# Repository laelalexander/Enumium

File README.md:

# Enumium
Official repository for the Enumium protocol, parent chain architecture, Pulse Network, and SiloBlockchain implementation lineage.

## Robot arm design package
Blueprints, part drawings, wiring schematic and CAD for the desktop robot arm: [`docs/design/README.md`](docs/design/README.md). Generator code: [`3d-workflow/`](3d-workflow/README.md).

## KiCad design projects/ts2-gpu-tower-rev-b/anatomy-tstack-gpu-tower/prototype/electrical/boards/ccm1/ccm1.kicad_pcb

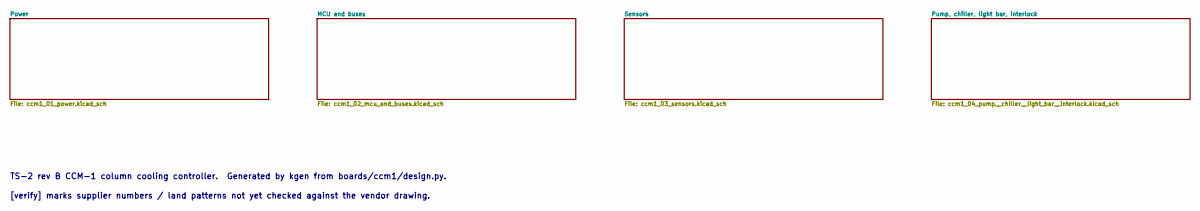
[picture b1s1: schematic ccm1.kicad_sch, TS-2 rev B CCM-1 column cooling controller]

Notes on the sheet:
TS-2 rev B CCM-1 column cooling controller. Generated by kgen from boards/ccm1/design.py.
[verify] marks supplier numbers / land patterns not yet checked against the vendor drawing.

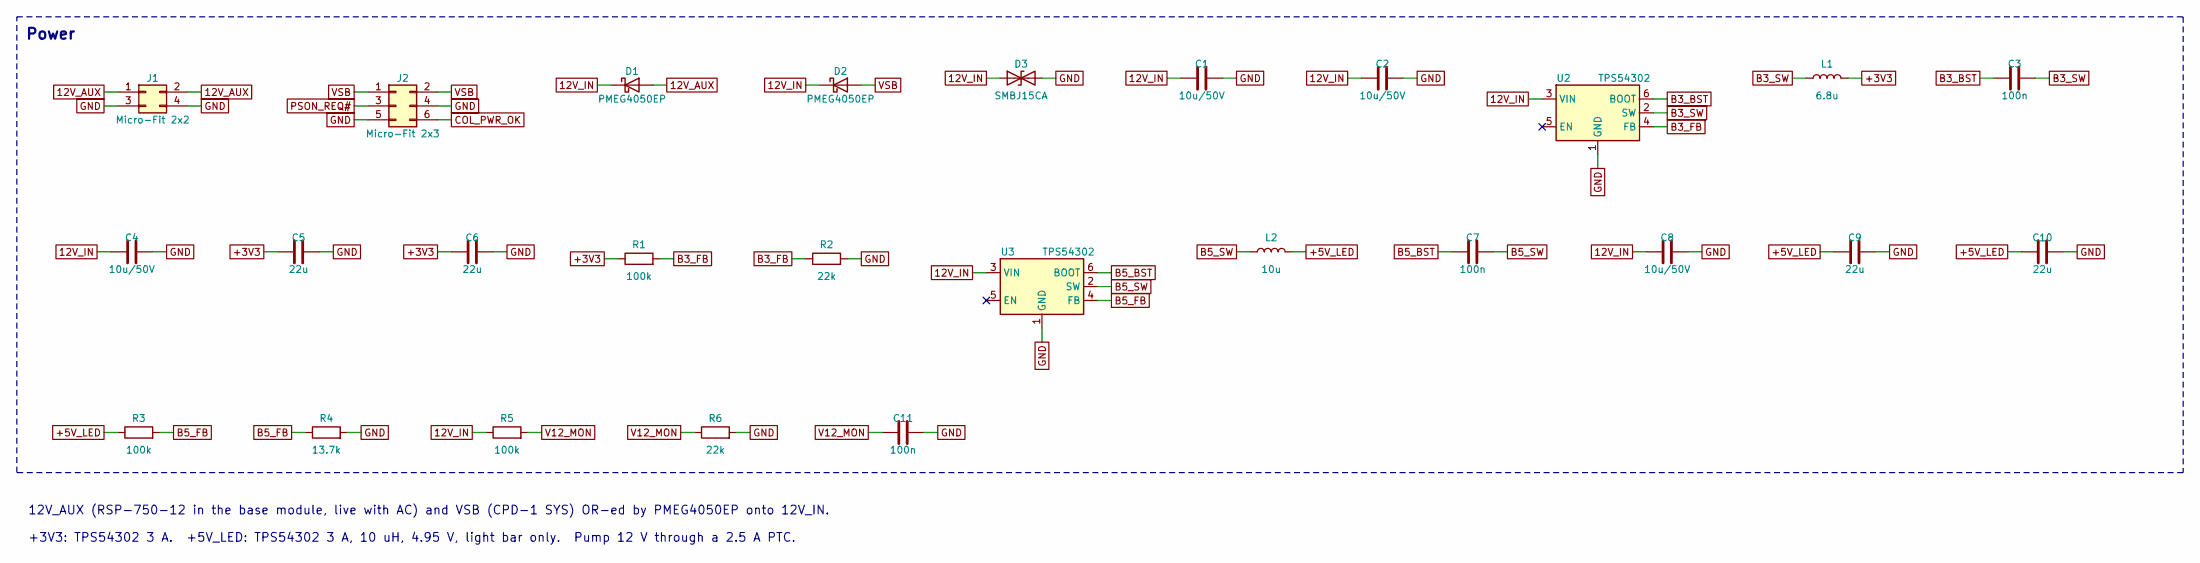
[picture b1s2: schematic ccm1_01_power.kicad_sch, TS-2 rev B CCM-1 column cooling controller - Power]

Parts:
C1, C2, C4, C8: 10u/50V; C_1206_3216Metric; MPN GRM31CR61H106KA12L; LCSC C13585
C3, C7, C11: 100n; C_0603_1608Metric; MPN CL10B104KB8NNNC; LCSC C1591
C5, C6, C9, C10: 22u; C_0805_2012Metric; MPN CL21A226MAQNNNE; LCSC C45783
D1, D2: PMEG4050EP; D_SOD-128; MPN PMEG4050EP,115
D3: SMBJ15CA; D_SMB; MPN SMBJ15CA
J1: Micro-Fit 2x2; Molex_Micro-Fit_3.0_43045-0412_2x02_P3.00mm_Vertical; MPN 43045-0412
J2: Micro-Fit 2x3; Molex_Micro-Fit_3.0_43045-0612_2x03_P3.00mm_Vertical; MPN 43045-0612
L1: 6.8u; L_Bourns_SRP7028A_7.3x6.6mm; MPN SRP7028A-6R8M
L2: 10u; L_Bourns_SRP7028A_7.3x6.6mm; MPN SRP7028A-100M
R1, R3, R5: 100k; R_0603_1608Metric; MPN 0603WAF1003T5E; LCSC C25803
R2, R6: 22k; R_0603_1608Metric; MPN 0603WAF2202T5E; LCSC C31850
R4: 13.7k; R_0603_1608Metric; MPN 0603WAF1372T5E; LCSC C22959
U2, U3: TPS54302; SOT-23-6; MPN TPS54302DDCR

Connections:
12V_AUX: D1.2 (A), J1.1, J1.2
12V_IN: C1.1, C2.1, C4.1, C8.1, D1.1 (K), D2.1 (K), D3.1 (A1), R5.1, U2.3 (VIN), U3.3 (VIN); also elsewhere on the board
+3V3: C5.1, C6.1, L1.2, R1.1; also elsewhere on the board
+5V_LED: C9.1, C10.1, L2.2, R3.1; also elsewhere on the board
B3_BST: C3.1, U2.6 (BOOT)
B3_FB: R1.2, R2.1, U2.4 (FB)
B3_SW: C3.2, L1.1, U2.2 (SW)
B5_BST: C7.1, U3.6 (BOOT)
B5_FB: R3.2, R4.1, U3.4 (FB)
B5_SW: C7.2, L2.1, U3.2 (SW)
COL_PWR_OK: J2.6; also elsewhere on the board
GND: C1.2, C2.2, C4.2, C5.2, C6.2, C8.2, C9.2, C10.2, C11.2, D3.2 (A2), J1.3, J1.4, J2.4, J2.5, R2.2, R4.2, R6.2, U2.1 (GND), U3.1 (GND); also elsewhere on the board
PSON_REQ#: J2.3; also elsewhere on the board
V12_MON: C11.1, R5.2, R6.1; also elsewhere on the board
VSB: D2.2 (A), J2.1, J2.2

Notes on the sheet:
Power
12V_AUX (RSP-750-12 in the base module, live with AC) and VSB (CPD-1 SYS) OR-ed by PMEG4050EP onto 12V_IN.
+3V3: TPS54302 3 A. +5V_LED: TPS54302 3 A, 10 uH, 4.95 V, light bar only. Pump 12 V through a 2.5 A PTC.

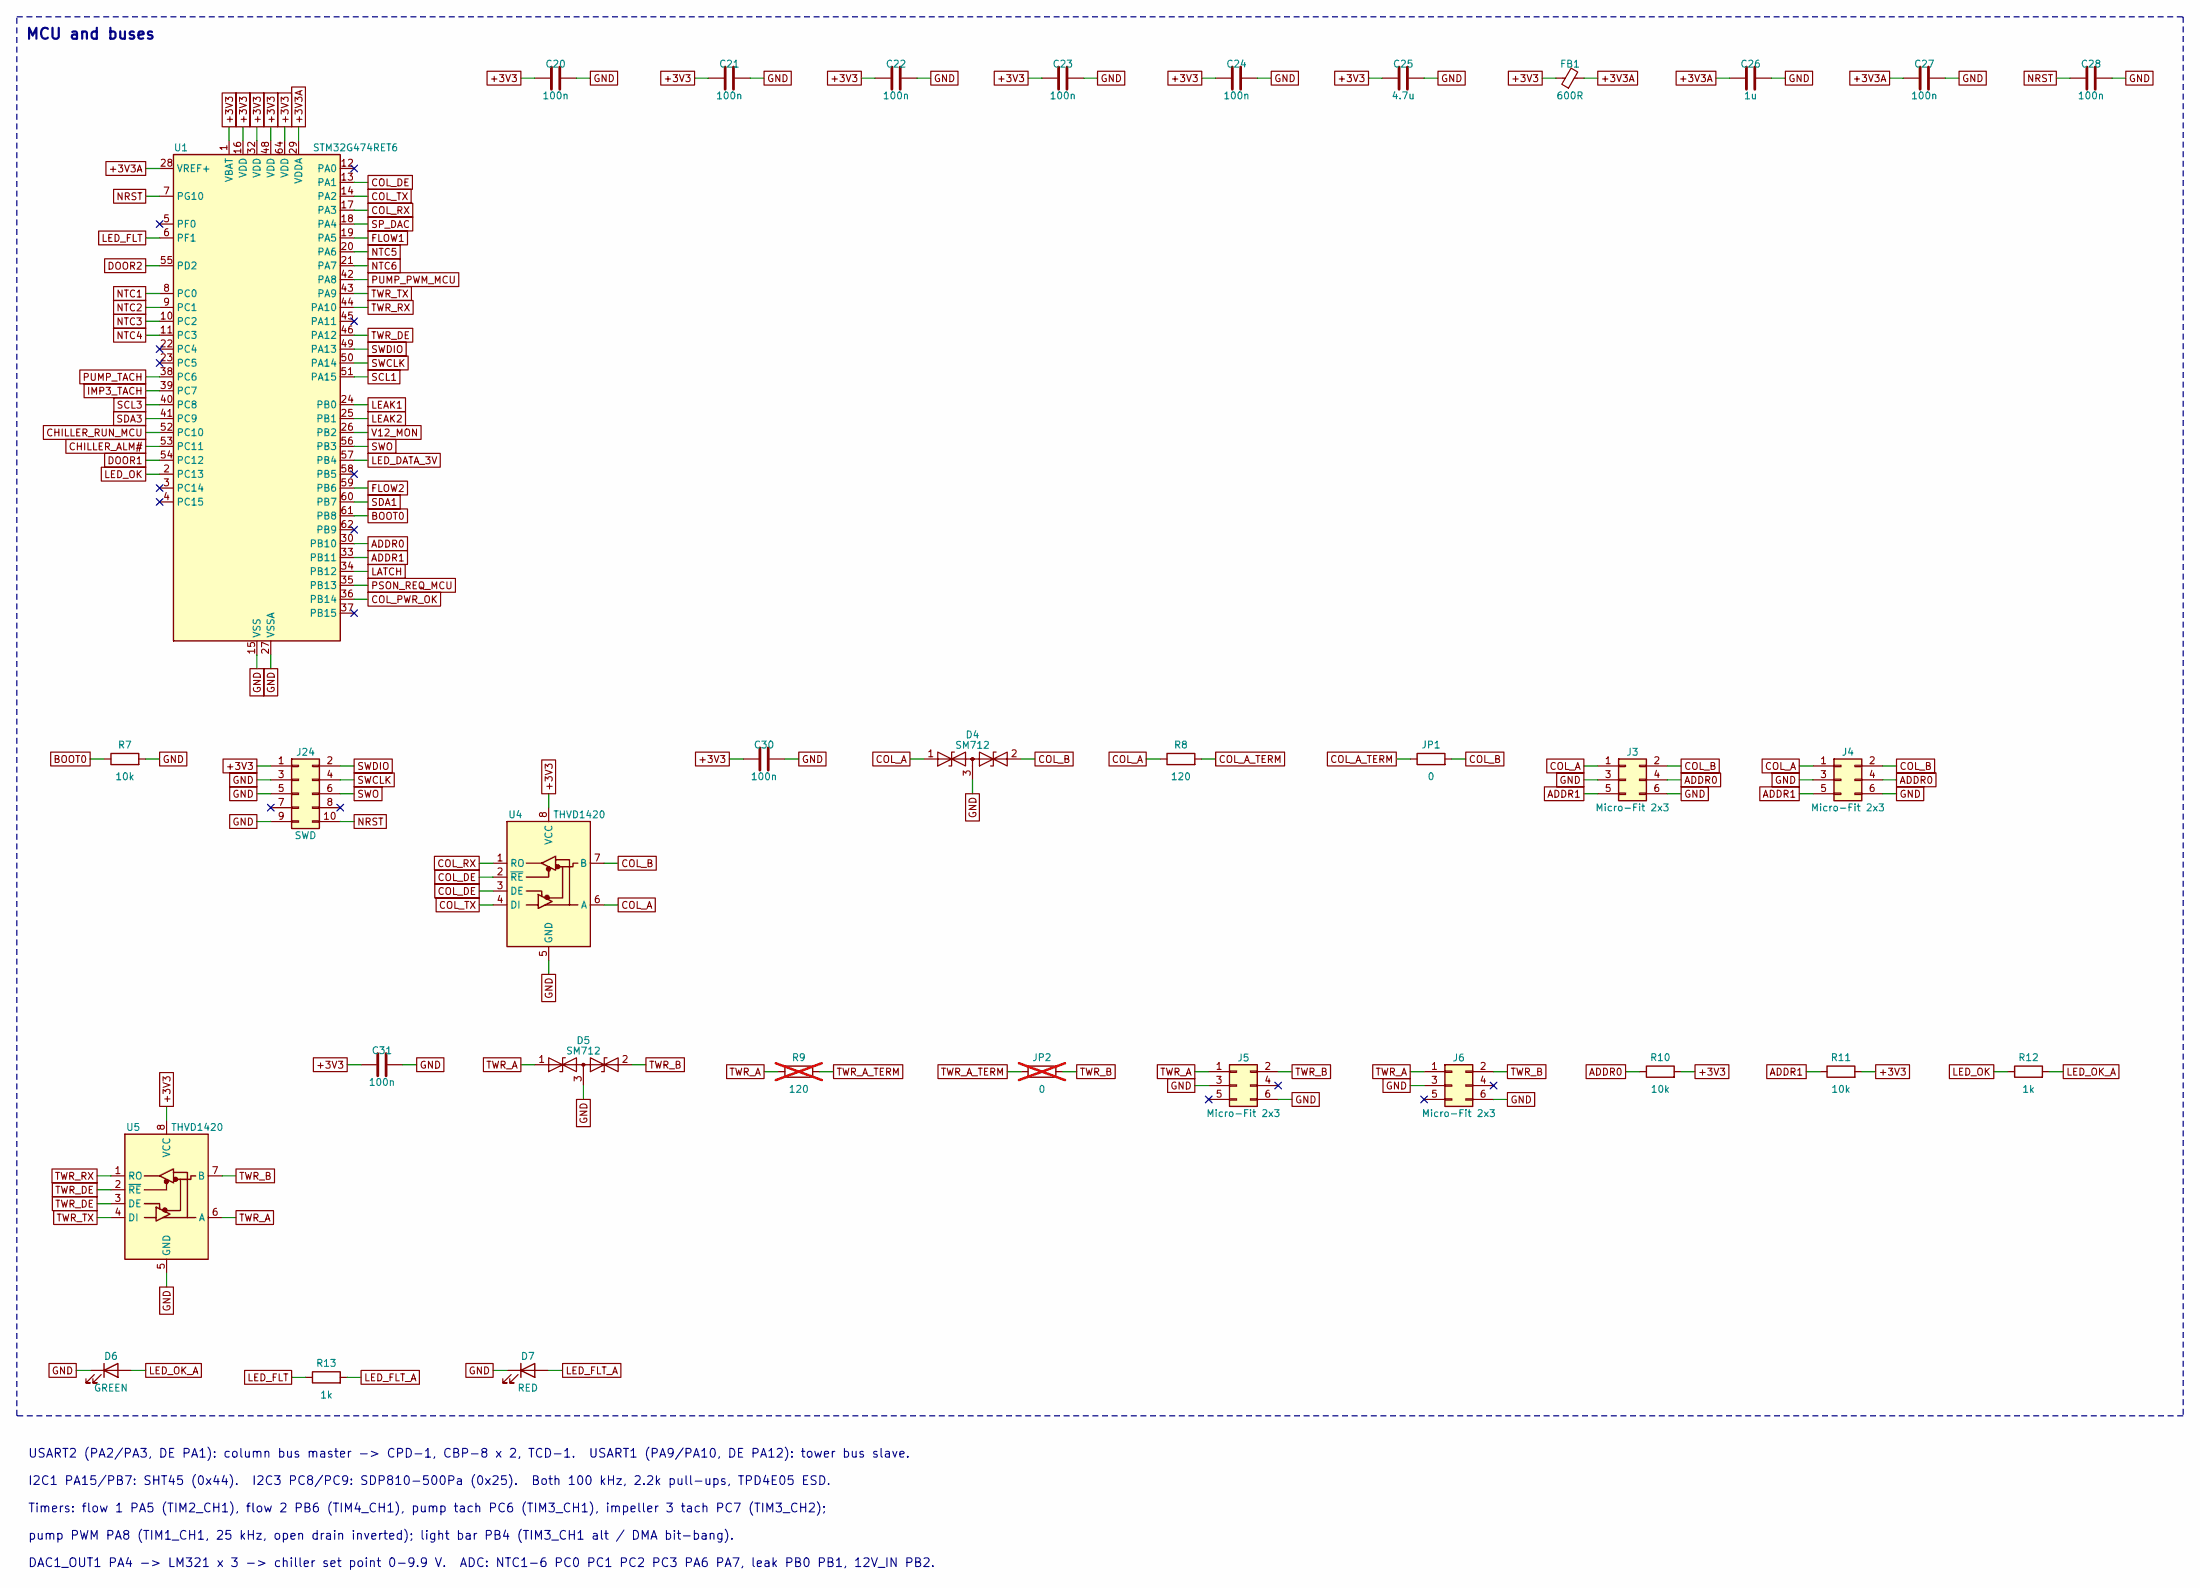
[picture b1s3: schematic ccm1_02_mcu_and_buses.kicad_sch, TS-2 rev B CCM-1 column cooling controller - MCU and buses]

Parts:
C20, C21, C22, C23, C24, C27, C28, C30, C31: 100n; C_0603_1608Metric; MPN CL10B104KB8NNNC; LCSC C1591
C25: 4.7u; C_0603_1608Metric; MPN CL10A475KO8NNNC; LCSC C19666
C26: 1u; C_0603_1608Metric; MPN CL10A105KA8NNNC; LCSC C15849
D4, D5: SM712; SOT-23; MPN SM712.TCT
D6: GREEN; LED_0603_1608Metric; MPN 150060VS75000
D7: RED; LED_0603_1608Metric; MPN 150060RS75000
FB1: 600R; L_0603_1608Metric; MPN BLM18KG601SN1D
J3, J4, J5, J6: Micro-Fit 2x3; Molex_Micro-Fit_3.0_43045-0612_2x03_P3.00mm_Vertical; MPN 43045-0612
J24: SWD; PinHeader_2x05_P1.27mm_Vertical; MPN FTSH-105-01-F-DV-K
JP1: 0; R_0603_1608Metric; MPN 0603WAF0000T5E
JP2: 0; R_0603_1608Metric; MPN 0603WAF0000T5E; not fitted
R7, R10, R11: 10k; R_0603_1608Metric; MPN 0603WAF1002T5E; LCSC C25804
R8: 120; R_0603_1608Metric; MPN 0603WAF1200T5E; LCSC C22787
R9: 120; R_0603_1608Metric; MPN 0603WAF1200T5E; LCSC C22787; not fitted
R12, R13: 1k; R_0603_1608Metric; MPN 0603WAF1001T5E; LCSC C21190
U1: STM32G474RET6; LQFP-64_10x10mm_P0.5mm; MPN STM32G474RET6
U4, U5: THVD1420; SOIC-8_3.9x4.9mm_P1.27mm; MPN THVD1420DR

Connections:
+3V3: C20.1, C21.1, C22.1, C23.1, C24.1, C25.1, C30.1, C31.1, FB1.1, J24.1, R10.2, R11.2, U1.1 (VBAT), U1.16 (VDD), U1.32 (VDD), U1.48 (VDD), U1.64 (VDD), U4.8 (VCC), U5.8 (VCC); also elsewhere on the board
+3V3A: C26.1, C27.1, FB1.2, U1.28 (VREF+), U1.29 (VDDA); also elsewhere on the board
ADDR0: J3.4, J4.4, R10.1, U1.30 (PB10)
ADDR1: J3.5, J4.5, R11.1, U1.33 (PB11)
BOOT0: R7.1, U1.61 (PB8)
CHILLER_ALM#: U1.53 (PC11); also elsewhere on the board
CHILLER_RUN_MCU: U1.52 (PC10); also elsewhere on the board
COL_A: D4.1 (A1), J3.1, J4.1, R8.1, U4.6 (A)
COL_A_TERM: JP1.1, R8.2
COL_B: D4.2 (A2), J3.2, J4.2, JP1.2, U4.7 (B)
COL_DE: U1.13 (PA1), U4.2 (~RE), U4.3 (DE)
COL_PWR_OK: U1.36 (PB14); also elsewhere on the board
COL_RX: U1.17 (PA3), U4.1 (RO)
COL_TX: U1.14 (PA2), U4.4 (DI)
DOOR1: U1.54 (PC12); also elsewhere on the board
DOOR2: U1.55 (PD2); also elsewhere on the board
FLOW1: U1.19 (PA5); also elsewhere on the board
FLOW2: U1.59 (PB6); also elsewhere on the board
GND: C20.2, C21.2, C22.2, C23.2, C24.2, C25.2, C26.2, C27.2, C28.2, C30.2, C31.2, D4.3 (common), D5.3 (common), D6.1 (K), D7.1 (K), J3.3, J3.6, J4.3, J4.6, J5.3, J5.6, J6.3, J6.6, J24.3, J24.5, J24.9, R7.2, U1.15 (VSS), U1.27 (VSSA), U1.31 (VSS), U1.47 (VSS), U1.63 (VSS), U4.5 (GND), U5.5 (GND); also elsewhere on the board
IMP3_TACH: U1.39 (PC7); also elsewhere on the board
LATCH: U1.34 (PB12); also elsewhere on the board
LEAK1: U1.24 (PB0); also elsewhere on the board
LEAK2: U1.25 (PB1); also elsewhere on the board
LED_DATA_3V: U1.57 (PB4); also elsewhere on the board
LED_FLT: R13.1, U1.6 (PF1)
LED_FLT_A: D7.2 (A), R13.2
LED_OK: R12.1, U1.2 (PC13)
LED_OK_A: D6.2 (A), R12.2
NRST: C28.1, J24.10, U1.7 (PG10)
NTC1: U1.8 (PC0); also elsewhere on the board
NTC2: U1.9 (PC1); also elsewhere on the board
NTC3: U1.10 (PC2); also elsewhere on the board
NTC4: U1.11 (PC3); also elsewhere on the board
NTC5: U1.20 (PA6); also elsewhere on the board
NTC6: U1.21 (PA7); also elsewhere on the board
PSON_REQ_MCU: U1.35 (PB13); also elsewhere on the board
PUMP_PWM_MCU: U1.42 (PA8); also elsewhere on the board
PUMP_TACH: U1.38 (PC6); also elsewhere on the board
SCL1: U1.51 (PA15); also elsewhere on the board
SCL3: U1.40 (PC8); also elsewhere on the board
SDA1: U1.60 (PB7); also elsewhere on the board
SDA3: U1.41 (PC9); also elsewhere on the board
SP_DAC: U1.18 (PA4); also elsewhere on the board
SWCLK: J24.4, U1.50 (PA14)
SWDIO: J24.2, U1.49 (PA13)
SWO: J24.6, U1.56 (PB3)
TWR_A: D5.1 (A1), J5.1, J6.1, R9.1, U5.6 (A)
TWR_A_TERM: JP2.1, R9.2
TWR_B: D5.2 (A2), J5.2, J6.2, JP2.2, U5.7 (B)
TWR_DE: U1.46 (PA12), U5.2 (~RE), U5.3 (DE)
TWR_RX: U1.44 (PA10), U5.1 (RO)
TWR_TX: U1.43 (PA9), U5.4 (DI)
V12_MON: U1.26 (PB2); also elsewhere on the board

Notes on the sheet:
MCU and buses
USART2 (PA2/PA3, DE PA1): column bus master -> CPD-1, CBP-8 x 2, TCD-1. USART1 (PA9/PA10, DE PA12): tower bus slave.
I2C1 PA15/PB7: SHT45 (0x44). I2C3 PC8/PC9: SDP810-500Pa (0x25). Both 100 kHz, 2.2k pull-ups, TPD4E05 ESD.
Timers: flow 1 PA5 (TIM2_CH1), flow 2 PB6 (TIM4_CH1), pump tach PC6 (TIM3_CH1), impeller 3 tach PC7 (TIM3_CH2);
pump PWM PA8 (TIM1_CH1, 25 kHz, open drain inverted); light bar PB4 (TIM3_CH1 alt / DMA bit-bang).
DAC1_OUT1 PA4 -> LM321 x 3 -> chiller set point 0-9.9 V. ADC: NTC1-6 PC0 PC1 PC2 PC3 PA6 PA7, leak PB0 PB1, 12V_IN PB2.

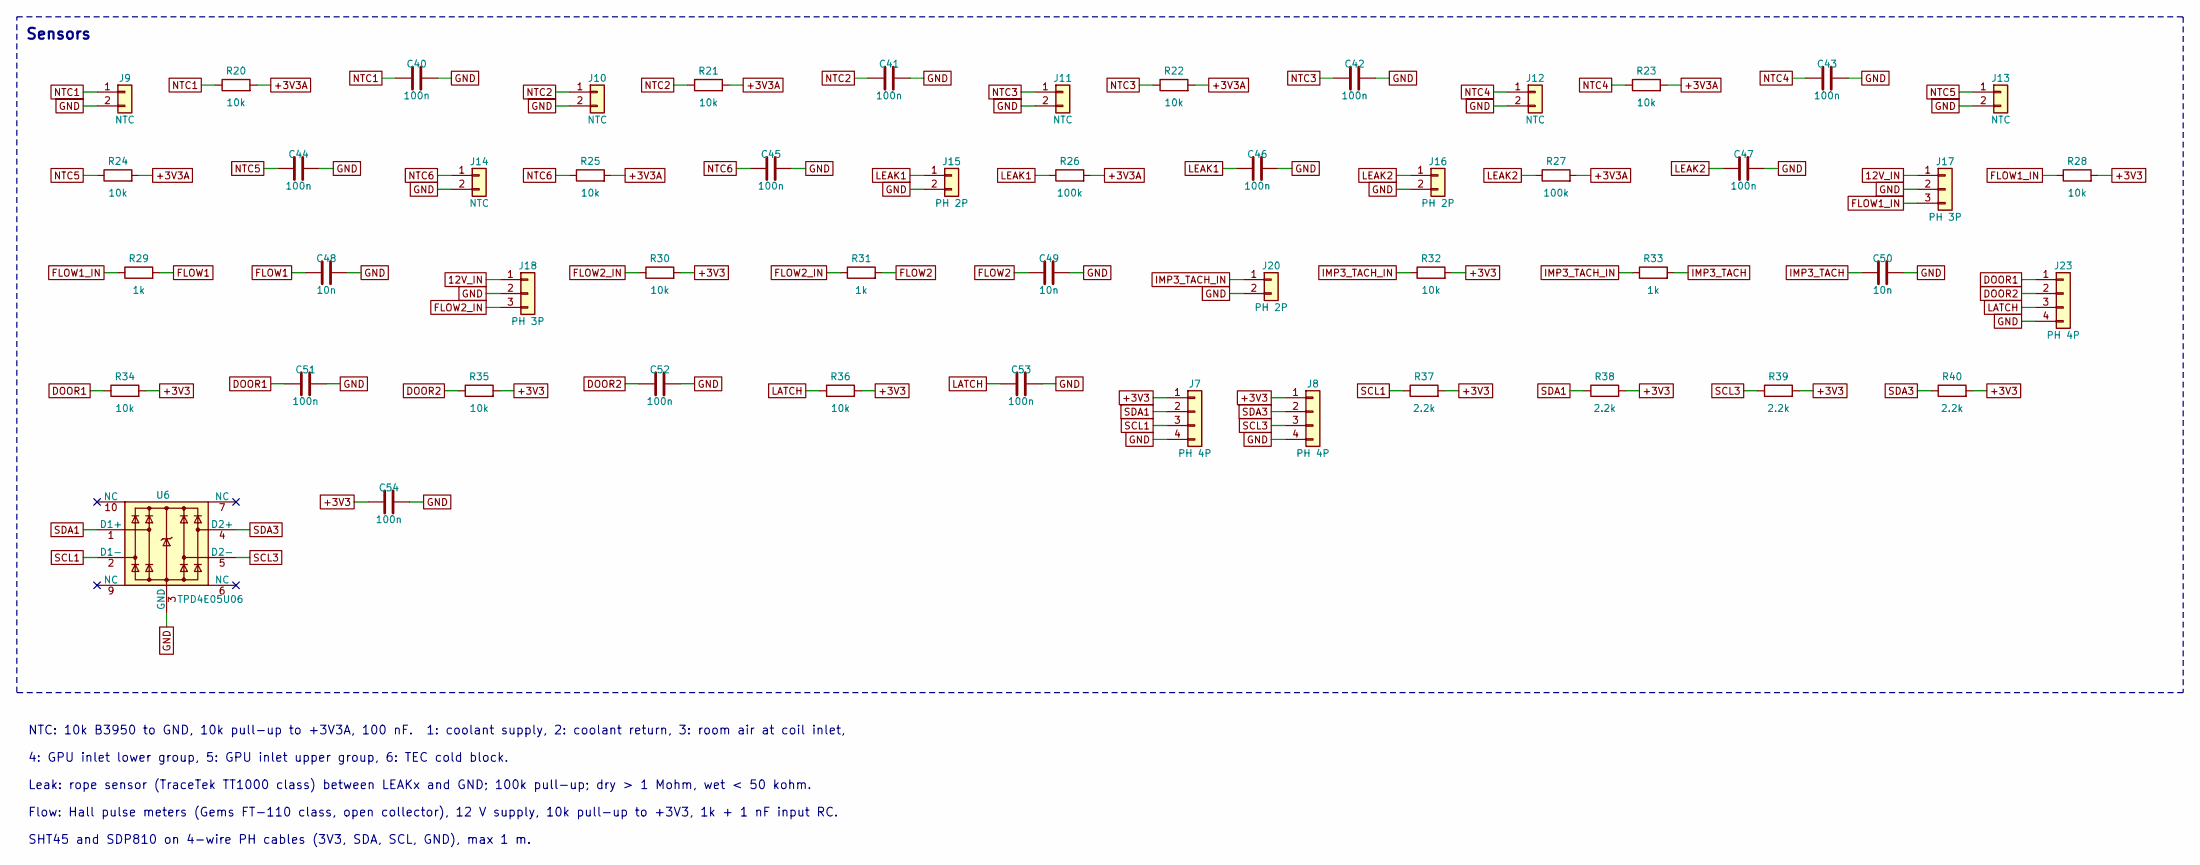
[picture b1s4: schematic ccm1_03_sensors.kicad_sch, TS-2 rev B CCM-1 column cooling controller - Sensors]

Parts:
C40, C41, C42, C43, C44, C45, C46, C47, C51, C52, C53, C54: 100n; C_0603_1608Metric; MPN CL10B104KB8NNNC; LCSC C1591
C48, C49, C50: 10n; C_0603_1608Metric; MPN CL10B103KB8NNNC; LCSC C57112
J7, J8, J23: PH 4P; JST_PH_B4B-PH-K_1x04_P2.00mm_Vertical; MPN B4B-PH-K-S
J9, J10, J11, J12, J13, J14: NTC; JST_PH_B2B-PH-K_1x02_P2.00mm_Vertical; MPN B2B-PH-K-S
J15, J16, J20: PH 2P; JST_PH_B2B-PH-K_1x02_P2.00mm_Vertical; MPN B2B-PH-K-S
J17, J18: PH 3P; JST_PH_B3B-PH-K_1x03_P2.00mm_Vertical; MPN B3B-PH-K-S
R20, R21, R22, R23, R24, R25, R28, R30, R32, R34, R35, R36: 10k; R_0603_1608Metric; MPN 0603WAF1002T5E; LCSC C25804
R26, R27: 100k; R_0603_1608Metric; MPN 0603WAF1003T5E; LCSC C25803
R29, R31, R33: 1k; R_0603_1608Metric; MPN 0603WAF1001T5E; LCSC C21190
R37, R38, R39, R40: 2.2k; R_0603_1608Metric; MPN 0603WAF2201T5E; LCSC C4190
U6: TPD4E05U06; USON-10_2.5x1.0mm_P0.5mm; MPN TPD4E05U06DQAR

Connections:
12V_IN: J17.1, J18.1; also elsewhere on the board
+3V3: C54.1, J7.1, J8.1, R28.2, R30.2, R32.2, R34.2, R35.2, R36.2, R37.2, R38.2, R39.2, R40.2; also elsewhere on the board
+3V3A: R20.2, R21.2, R22.2, R23.2, R24.2, R25.2, R26.2, R27.2; also elsewhere on the board
DOOR1: C51.1, J23.1, R34.1; also elsewhere on the board
DOOR2: C52.1, J23.2, R35.1; also elsewhere on the board
FLOW1: C48.1, R29.2; also elsewhere on the board
FLOW1_IN: J17.3, R28.1, R29.1
FLOW2: C49.1, R31.2; also elsewhere on the board
FLOW2_IN: J18.3, R30.1, R31.1
GND: C40.2, C41.2, C42.2, C43.2, C44.2, C45.2, C46.2, C47.2, C48.2, C49.2, C50.2, C51.2, C52.2, C53.2, C54.2, J7.4, J8.4, J9.2, J10.2, J11.2, J12.2, J13.2, J14.2, J15.2, J16.2, J17.2, J18.2, J20.2, J23.4, U6.3 (GND), U6.8 (GND); also elsewhere on the board
IMP3_TACH: C50.1, R33.2; also elsewhere on the board
IMP3_TACH_IN: J20.1, R32.1, R33.1
LATCH: C53.1, J23.3, R36.1; also elsewhere on the board
LEAK1: C46.1, J15.1, R26.1; also elsewhere on the board
LEAK2: C47.1, J16.1, R27.1; also elsewhere on the board
NTC1: C40.1, J9.1, R20.1; also elsewhere on the board
NTC2: C41.1, J10.1, R21.1; also elsewhere on the board
NTC3: C42.1, J11.1, R22.1; also elsewhere on the board
NTC4: C43.1, J12.1, R23.1; also elsewhere on the board
NTC5: C44.1, J13.1, R24.1; also elsewhere on the board
NTC6: C45.1, J14.1, R25.1; also elsewhere on the board
SCL1: J7.3, R37.1, U6.2 (D1-); also elsewhere on the board
SCL3: J8.3, R39.1, U6.5 (D2-); also elsewhere on the board
SDA1: J7.2, R38.1, U6.1 (D1+); also elsewhere on the board
SDA3: J8.2, R40.1, U6.4 (D2+); also elsewhere on the board

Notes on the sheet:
Sensors
NTC: 10k B3950 to GND, 10k pull-up to +3V3A, 100 nF. 1: coolant supply, 2: coolant return, 3: room air at coil inlet,
4: GPU inlet lower group, 5: GPU inlet upper group, 6: TEC cold block.
Leak: rope sensor (TraceTek TT1000 class) between LEAKx and GND; 100k pull-up; dry > 1 Mohm, wet < 50 kohm.
Flow: Hall pulse meters (Gems FT-110 class, open collector), 12 V supply, 10k pull-up to +3V3, 1k + 1 nF input RC.
SHT45 and SDP810 on 4-wire PH cables (3V3, SDA, SCL, GND), max 1 m.

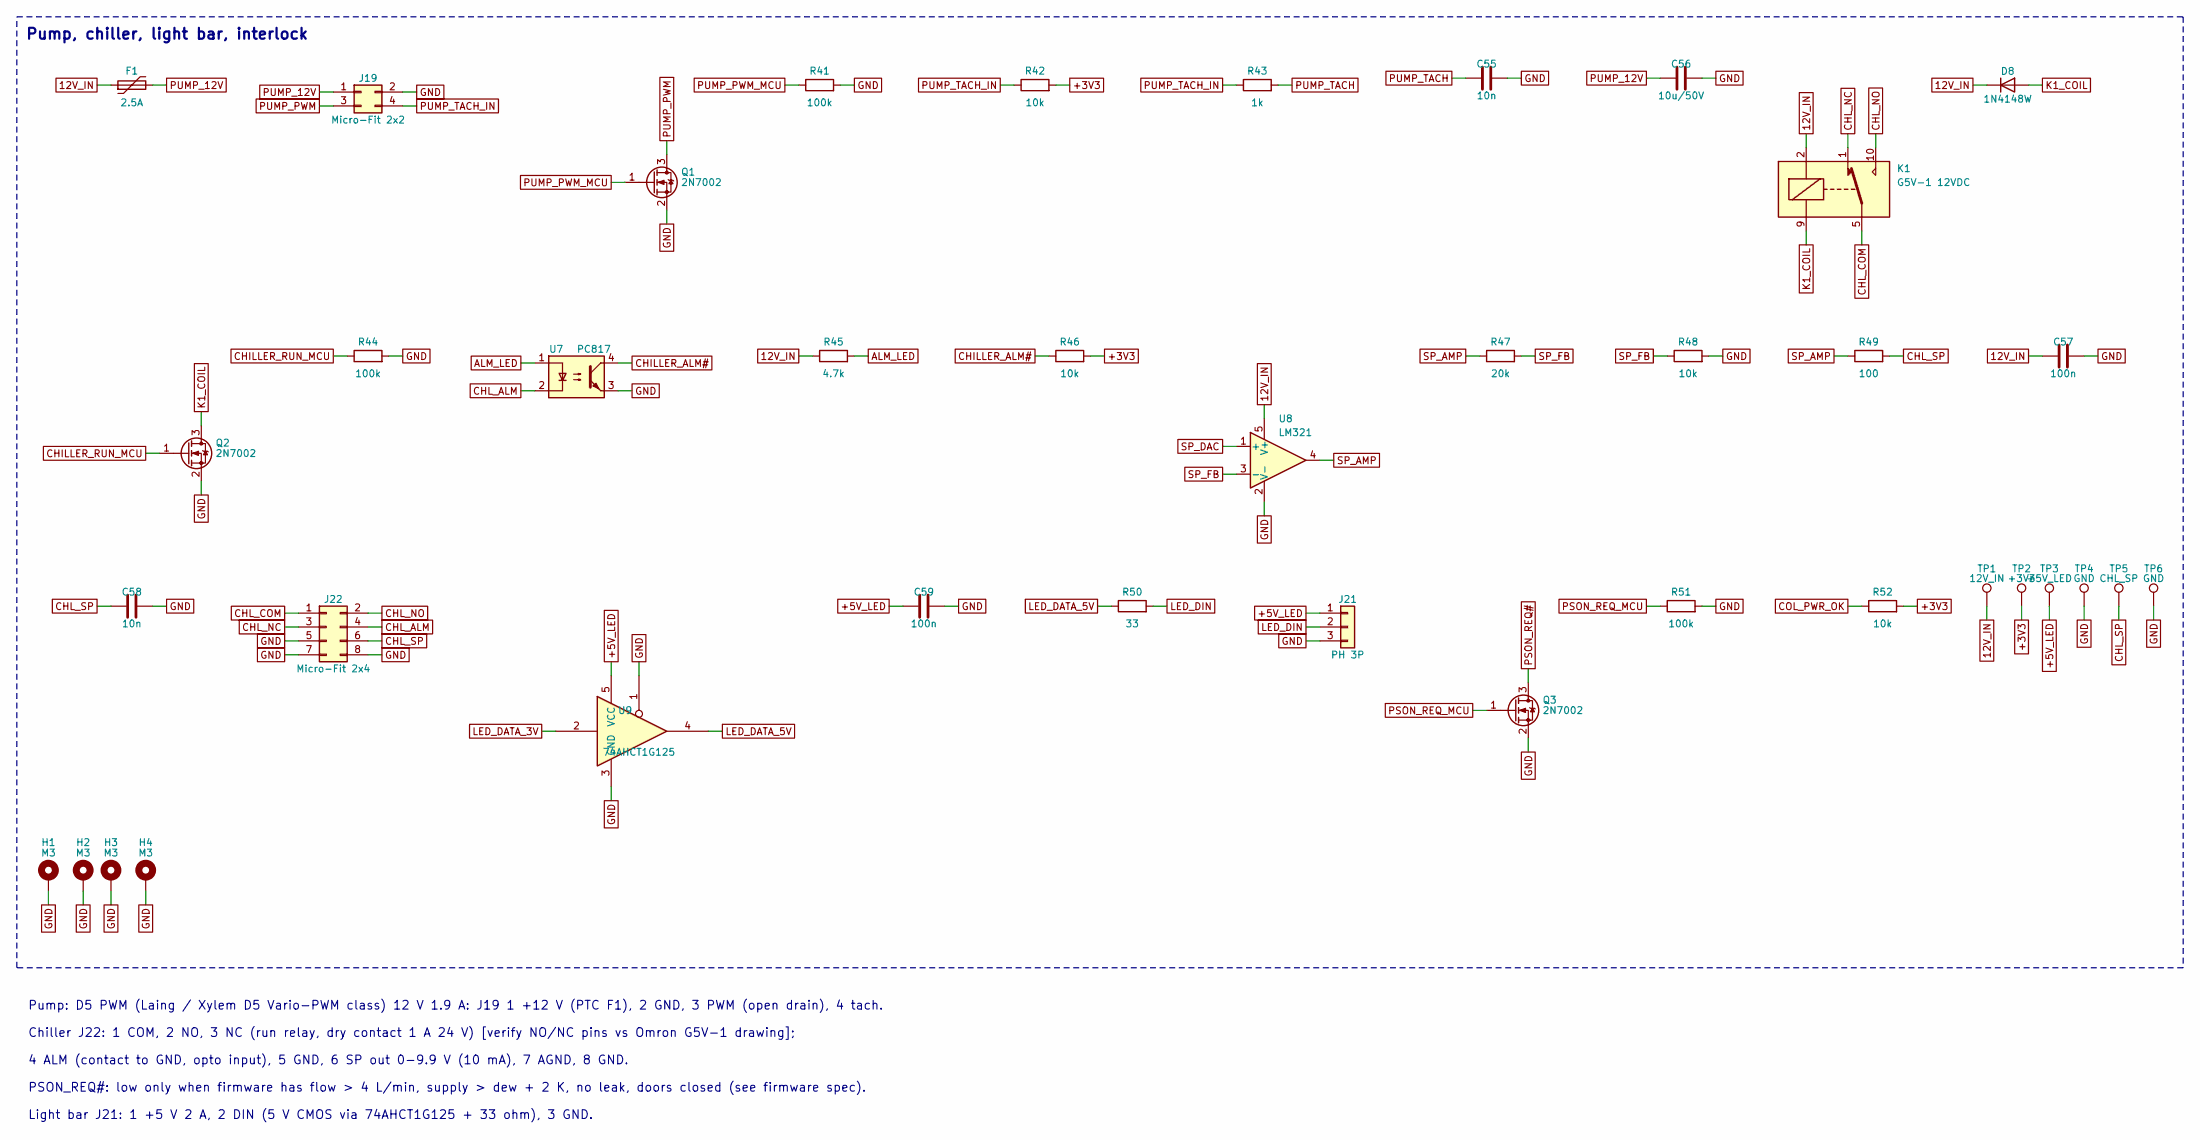
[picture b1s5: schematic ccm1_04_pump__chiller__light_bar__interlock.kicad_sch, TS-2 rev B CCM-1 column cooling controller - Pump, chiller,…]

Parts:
C55, C58: 10n; C_0603_1608Metric; MPN CL10B103KB8NNNC; LCSC C57112
C56: 10u/50V; C_1206_3216Metric; MPN GRM31CR61H106KA12L; LCSC C13585
C57, C59: 100n; C_0603_1608Metric; MPN CL10B104KB8NNNC; LCSC C1591
D8: 1N4148W; D_SOD-123; MPN 1N4148W-7-F
F1: 2.5A; Fuse_1812_4532Metric; MPN MF-MSMF250/16X-2
H1, H2, H3, H4: M3; MountingHole_3.2mm_M3_Pad_Via
J19: Micro-Fit 2x2; Molex_Micro-Fit_3.0_43045-0412_2x02_P3.00mm_Vertical; MPN 43045-0412
J21: PH 3P; JST_PH_B3B-PH-K_1x03_P2.00mm_Vertical; MPN B3B-PH-K-S
J22: Micro-Fit 2x4; Molex_Micro-Fit_3.0_43045-0812_2x04_P3.00mm_Vertical; MPN 43045-0812
K1: G5V-1 12VDC; Relay_SPDT_Omron_G5V-1; MPN G5V-1-DC12
Q1, Q2, Q3: 2N7002; SOT-23; MPN 2N7002,215
R41, R44, R51: 100k; R_0603_1608Metric; MPN 0603WAF1003T5E; LCSC C25803
R42, R46, R48, R52: 10k; R_0603_1608Metric; MPN 0603WAF1002T5E; LCSC C25804
R43: 1k; R_0603_1608Metric; MPN 0603WAF1001T5E; LCSC C21190
R45: 4.7k; R_0603_1608Metric; MPN 0603WAF4701T5E; LCSC C23162
R47: 20k; R_0603_1608Metric; MPN 0603WAF2002T5E; LCSC C4184
R49: 100; R_0603_1608Metric; MPN 0603WAF1000T5E; LCSC C22775
R50: 33; R_0603_1608Metric; MPN 0603WAF330JT5E; LCSC C23140
TP1: 12V_IN; TestPoint_Pad_D1.5mm
TP2: +3V3; TestPoint_Pad_D1.5mm
TP3: +5V_LED; TestPoint_Pad_D1.5mm
TP4, TP6: GND; TestPoint_Pad_D1.5mm
TP5: CHL_SP; TestPoint_Pad_D1.5mm
U7: PC817; SMDIP-4_W9.53mm; MPN PC817X2NSZ9F
U8: LM321; SOT-23-5; MPN LM321MF/NOPB
U9: 74AHCT1G125; SOT-23-5; MPN SN74AHCT1G125DBVR

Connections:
12V_IN: C57.1, D8.1 (K), F1.1, K1.2, R45.1, TP1.1, U8.5 (V+); also elsewhere on the board
+3V3: R42.2, R46.2, R52.2, TP2.1; also elsewhere on the board
+5V_LED: C59.1, J21.1, TP3.1, U9.5 (VCC); also elsewhere on the board
ALM_LED: R45.2, U7.1
CHILLER_ALM#: R46.1, U7.4; also elsewhere on the board
CHILLER_RUN_MCU: Q2.1 (G), R44.1; also elsewhere on the board
CHL_ALM: J22.4, U7.2
CHL_COM: J22.1, K1.5, K1.6
CHL_NC: J22.3, K1.1
CHL_NO: J22.2, K1.10
CHL_SP: C58.1, J22.6, R49.2, TP5.1
COL_PWR_OK: R52.1; also elsewhere on the board
GND: C55.2, C56.2, C57.2, C58.2, C59.2, H1.1, H2.1, H3.1, H4.1, J19.2, J21.3, J22.5, J22.7, J22.8, Q1.2 (S), Q2.2 (S), Q3.2 (S), R41.2, R44.2, R48.2, R51.2, TP4.1, TP6.1, U7.3, U8.2 (V-), U9.1, U9.3 (GND); also elsewhere on the board
K1_COIL: D8.2 (A), K1.9, Q2.3 (D)
LED_DATA_3V: U9.2; also elsewhere on the board
LED_DATA_5V: R50.1, U9.4
LED_DIN: J21.2, R50.2
PSON_REQ#: Q3.3 (D); also elsewhere on the board
PSON_REQ_MCU: Q3.1 (G), R51.1; also elsewhere on the board
PUMP_12V: C56.1, F1.2, J19.1
PUMP_PWM: J19.3, Q1.3 (D)
PUMP_PWM_MCU: Q1.1 (G), R41.1; also elsewhere on the board
PUMP_TACH: C55.1, R43.2; also elsewhere on the board
PUMP_TACH_IN: J19.4, R42.1, R43.1
SP_AMP: R47.1, R49.1, U8.4
SP_DAC: U8.1 (+); also elsewhere on the board
SP_FB: R47.2, R48.1, U8.3 (-)

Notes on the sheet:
Pump, chiller, light bar, interlock
Pump: D5 PWM (Laing / Xylem D5 Vario-PWM class) 12 V 1.9 A: J19 1 +12 V (PTC F1), 2 GND, 3 PWM (open drain), 4 tach.
Chiller J22: 1 COM, 2 NO, 3 NC (run relay, dry contact 1 A 24 V) [verify NO/NC pins vs Omron G5V-1 drawing];
4 ALM (contact to GND, opto input), 5 GND, 6 SP out 0-9.9 V (10 mA), 7 AGND, 8 GND.
PSON_REQ#: low only when firmware has flow > 4 L/min, supply > dew + 2 K, no leak, doors closed (see firmware spec).
Light bar J21: 1 +5 V 2 A, 2 DIN (5 V CMOS via 74AHCT1G125 + 33 ohm), 3 GND.

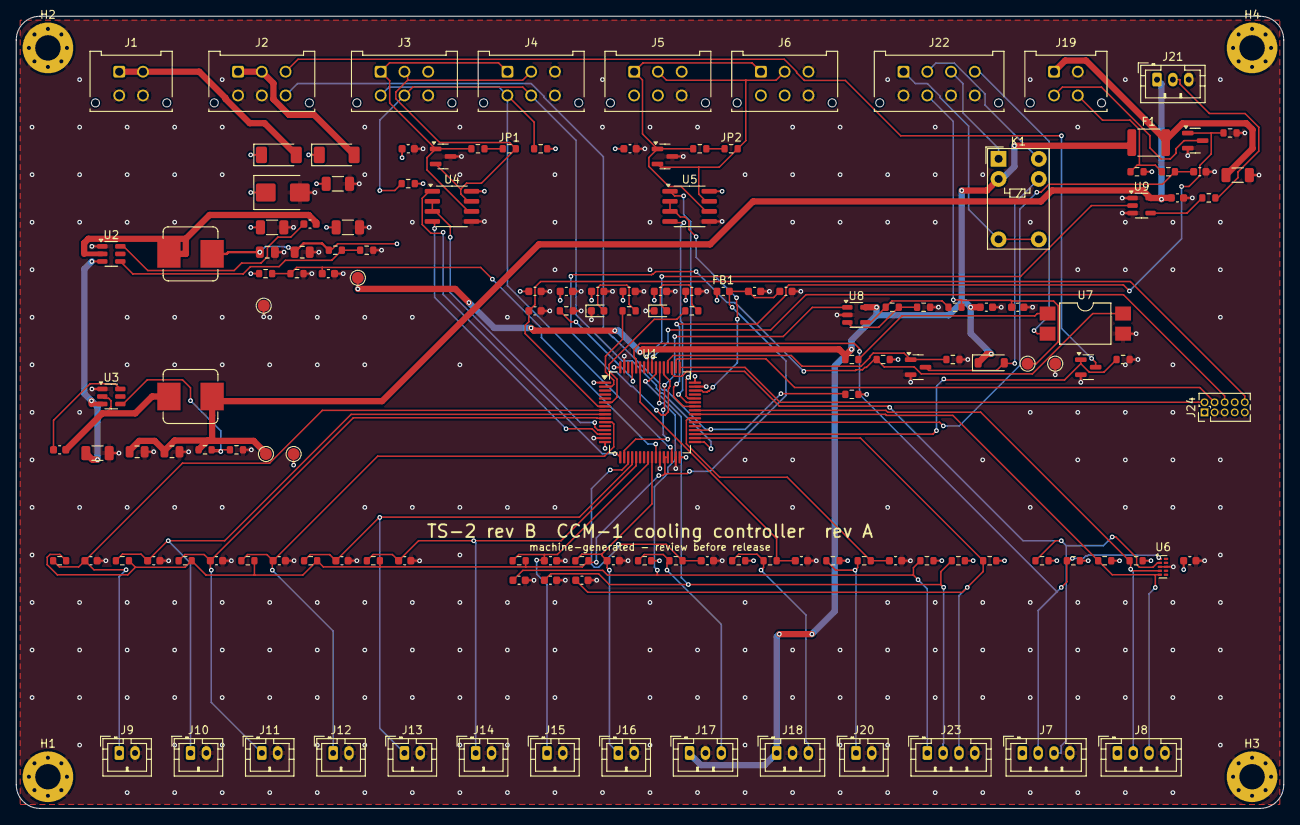
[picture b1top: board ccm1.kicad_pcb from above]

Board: 4 copper layers, 160.0 x 100.0 mm, 149 parts (0 on the bottom side), 81 nets.

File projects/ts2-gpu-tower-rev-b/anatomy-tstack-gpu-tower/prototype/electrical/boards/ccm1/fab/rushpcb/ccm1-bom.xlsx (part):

CCM1 TS-2 rev B CCM-1 column cooling controller rev A - Bill of Materials (qty 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
Item | Qty | Designators | Value | Description | Manufacturer | MPN | Supplier PN | Footprint | Side | DNP | Unit price USD (est.) | Ext. USD (est.)
1 | 5 | C1 C2 C4 C8 C56 | 10u/50V | MLCC 10 uF 50 V X5R 1206 | Murata | GRM31CR61H106KA12L | LCSC C13585 | C_1206_3216Metric | Top |  | 0.06 | 0.3
2 | 4 | C5 C6 C9 C10 | 22u | MLCC 22 uF 25 V X5R 0805 | Samsung Electro-Mechanics | CL21A226MAQNNNE | LCSC C45783 | C_0805_2012Metric | Top |  | 0.06 | 0.24
3 | 26 | C3 C7 C11 C20 C21 C22 C23 C24 C27 C28 C30 C31 C40 C41 C42 C43 C44 C45 C46 C47 C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 | 100n | Bootstrap 100 nF | Samsung Electro-Mechanics | CL10B104KB8NNNC | LCSC C1591 | C_0603_1608Metric | Top |  | 0.01 | 0.26
4 | 1 | C25 | 4.7u | MLCC 4.7 uF 16 V X5R 0603 | Samsung Electro-Mechanics | CL10A475KO8NNNC | LCSC C19666 | C_0603_1608Metric | Top |  | 0.01 | 0.01
5 | 1 | C26 | 1u | VDDA decoupling | Samsung Electro-Mechanics | CL10A105KA8NNNC | LCSC C15849 | C_0603_1608Metric | Top |  | 0.01 | 0.01
6 | 5 | C48 C49 C50 C55 C58 | 10n | input filter (pulses < 2 kHz) | Samsung Electro-Mechanics | CL10B103KB8NNNC | LCSC C57112 | C_0603_1608Metric | Top |  | 0.01 | 0.05
7 | 2 | D1 D2 | PMEG4050EP | Schottky 40 V 5 A SOD-128, supply OR-ing | Nexperia | PMEG4050EP,115 | 1727-4993-1-ND [verify] | D_SOD-128 | Top |  | 0.35 | 0.7
8 | 1 | D3 | SMBJ15CA | TVS 15 V 600 W, 12V_IN | Littelfuse | SMBJ15CA | SMBJ15CALFCT-ND [verify] | D_SMB | Top |  | 0.3 | 0.3
9 | 2 | D4 D5 | SM712 | RS-485 TVS -7 / +12 V asymmetric | Semtech | SM712.TCT | SM712.TCTCT-ND [verify] | SOT-23 | Top |  | 0.4 | 0.8
10 | 1 | D6 | GREEN | LED green 0603 | Wurth Elektronik | 150060VS75000 | [verify] | LED_0603_1608Metric | Top |  | 0.15 | 0.15
11 | 1 | D7 | RED | LED red 0603 | Wurth Elektronik | 150060RS75000 | [verify] | LED_0603_1608Metric | Top |  | 0.15 | 0.15
12 | 1 | D8 | 1N4148W | Relay coil flyback | Diodes Inc | 1N4148W-7-F | 1N4148W-FDICT-ND | D_SOD-123 | Top |  | 0.05 | 0.05
13 | 1 | F1 | 2.5A | PTC 2.5 A hold 16 V 1812, pump supply | Bourns | MF-MSMF250/16X-2 | MF-MSMF250/16X-2CT-ND [verify] | Fuse_1812_4532Metric | Top |  | 0.4 | 0.4
14 | 1 | FB1 | 600R | Ferrite 600 ohm @ 100 MHz, VDDA / VREF+ filter | Murata | BLM18KG601SN1D | 490-5258-1-ND [verify] | L_0603_1608Metric | Top |  | 0.1 | 0.1
15 | 2 | J1 J19 | Micro-Fit 2x2 | 12V_AUX in from RSP-750-12: 1/2 +12 V, 3/4 GND (mating 43025-0400 + 43030 crimp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 | Molex | 43045-0412 | [verify] | Molex_Micro-Fit_3.0_43045-0412_2x02_P3.00mm_Vertical | Top |  | 1.2 | 2.4
16 | 5 | J2 J3 J4 J5 J6 | Micro-Fit 2x3 | CPD-1 SYS: 1/2 VSB in, 3 PSON_REQ# out (open drain), 4/5 GND, 6 COL_PWR_OK in (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 | Molex | 43045-0612 | [verify] | Molex_Micro-Fit_3.0_43045-0612_2x03_P3.00mm_Vertical | Top |  | 1.2 | 6
17 | 6 | J9 J10 J11 J12 J13 J14 | NTC | NTC 10k B3950 cable sensor: coolant supply | JST | B2B-PH-K-S | 455-1704-ND | JST_PH_B2B-PH-K_1x02_P2.00mm_Vertical | Top |  | 0.2 | 1.2
18 | 3 | J15 J16 J20 | PH 2P | Leak rope sensor 1 (coil drip tray) (mating PHR-2 + SPH-002T-P0.5S) | JST | B2B-PH-K-S | [verify] | JST_PH_B2B-PH-K_1x02_P2.00mm_Vertical | Top |  | 0.2 | 0.6
19 | 3 | J17 J18 J21 | PH 3P | Flow meter 1 (column supply): 1 +12 V, 2 GND, 3 pulse (mating PHR-3 + SPH-002T-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 | JST | B3B-PH-K-S | [verify] | JST_PH_B3B-PH-K_1x03_P2.00mm_Vertical | Top |  | 0.2 | 0.6
20 | 1 | J22 | Micro-Fit 2x4 | Chiller: 1 COM, 2 NO, 3 NC, 4 ALM, 5 GND, 6 SP 0-9.9 V, 7 AGND, 8 GND (mating 4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 | Molex | 43045-0812 | [verify] | Molex_Micro-Fit_3.0_43045-0812_2x04_P3.00mm_Vertical | Top |  | 1.2 | 1.2
21 | 3 | J7 J8 J23 | PH 4P | Switches to GND: 1 service door, 2 crown access, 3 coil latch (mating PHR-4 + S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 | JST | B4B-PH-K-S | [verify] | JST_PH_B4B-PH-K_1x04_P2.00mm_Vertical | Top |  | 0.2 | 0.6
22 | 1 | J24 | SWD | Arm Cortex debug 10-pin 1.27 mm (SWD + SWO), keyed | Samtec | FTSH-105-01-F-DV-K | SAM8796-ND [verify] | PinHeader_2x05_P1.27mm_Vertical | Top |  | 2.1 | 2.1
23 | 1 | JP1 | 0 | Termination link (fit with R8 on the end node) | UNI-ROYAL | 0603WAF0000T5E |  | R_0603_1608Metric | Top |  | 0 | 0
24 | 1 | JP2 | 0 | Termination link (fit with R9 on the end node) | UNI-ROYAL | 0603WAF0000T5E |  | R_0603_1608Metric | Top | DNP | 0 | 0
25 | 1 | K1 | G5V-1 12VDC | Relay SPDT 12 V coil 30 mA, 1 A 24 VDC contact, chiller remote run | Omron | G5V-1-DC12 | Z2296-ND [verify] | Relay_SPDT_Omron_G5V-1 | Top |  | 1.9 | 1.9
26 | 1 | L1 | 6.8u | Inductor 6.8 uH shielded 7.3 x 6.6 x 2.8 mm | Bourns | SRP7028A-6R8M | SRP7028A-6R8MCT-ND [verify] | L_Bourns_SRP7028A_7.3x6.6mm | Top |  | 0.6 | 0.6
27 | 1 | L2 | 10u | Inductor 10 uH shielded 7.3 x 6.6 x 2.8 mm | Bourns | SRP7028A-100M | SRP7028A-100MCT-ND [verify] | L_Bourns_SRP7028A_7.3x6.6mm | Top |  | 0.6 | 0.6
28 | 3 | Q1 Q2 Q3 | 2N7002 | N-MOSFET 60 V 0.3 A SOT-23, pump PWM open drain (inverted in firmware) | Nexperia | 2N7002,215 | 1727-2N7002215CT-ND | SOT-23 | Top |  | 0.05 | 0.15
29 | 8 | R1 R3 R5 R26 R27 R41 R44 R51 | 100k | FB top | UNI-ROYAL | 0603WAF1003T5E | LCSC C25803 | R_0603_1608Metric | Top |  | 0.002 | 0.02
30 | 2 | R2 R6 | 22k | FB bottom: 0.596 x (1 + 100k / 22k) | UNI-ROYAL | 0603WAF2202T5E | LCSC C31850 | R_0603_1608Metric | Top |  | 0.002 | 0
31 | 1 | R4 | 13.7k | FB bottom: 0.596 x (1 + 100k / 13.7k) | UNI-ROYAL | 0603WAF1372T5E | LCSC C22959 | R_0603_1608Metric | Top |  | 0.002 | 0
32 | 1 | R8 | 120 | Column bus termination 120 ohm - fitted: CCM-1 is the master at one end of the 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 | UNI-ROYAL | 0603WAF1200T5E | LCSC C22787 | R_0603_1608Metric | Top |  | 0.002 | 0
33 | 1 | R9 | 120 | Bus termination 120 ohm - fit on the end node only | UNI-ROYAL | 0603WAF1200T5E | LCSC C22787 | R_0603_1608Metric | Top | DNP | 0.002 | 0
34 | 19 | R7 R10 R11 R20 R21 R22 R23 R24 R25 R28 R30 R32 R34 R35 R36 R42 R46 R48 R52 | 10k | BOOT0 pull-down (boot from flash) | UNI-ROYAL | 0603WAF1002T5E | LCSC C25804 | R_0603_1608Metric | Top |  | 0.002 | 0.04
35 | 6 | R12 R13 R29 R31 R33 R43 | 1k | Resistor 1k 1% 0603 | UNI-ROYAL | 0603WAF1001T5E | LCSC C21190 | R_0603_1608Metric | Top |  | 0.002 | 0.01
36 | 4 | R37 R38 R39 R40 | 2.2k | I2C pull-up | UNI-ROYAL | 0603WAF2201T5E | LCSC C4190 | R_0603_1608Metric | Top |  | 0.002 | 0.01
37 | 1 | R45 | 4.7k | opto LED 2.4 mA | UNI-ROYAL | 0603WAF4701T5E | LCSC C23162 | R_0603_1608Metric | Top |  | 0.002 | 0
38 | 1 | R47 | 20k | gain 1 + 20k / 10k = 3 | UNI-ROYAL | 0603WAF2002T5E | LCSC C4184 | R_0603_1608Metric | Top |  | 0.002 | 0
39 | 1 | R49 | 100 | output isolation | UNI-ROYAL | 0603WAF1000T5E | LCSC C22775 | R_0603_1608Metric | Top |  | 0.002 | 0
40 | 1 | R50 | 33 | data series | UNI-ROYAL | 0603WAF330JT5E | LCSC C23140 | R_0603_1608Metric | Top |  | 0.002 | 0
41 | 1 | U1 | STM32G474RET6 | MCU Arm Cortex-M4F 170 MHz, 512 KB flash, LQFP-64 (pin map from the KiCad STM32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 | STMicroelectronics | STM32G474RET6 | 497-19525-ND [verify] | LQFP-64_10x10mm_P0.5mm | Top |  | 7.9 | 7.9
42 | 2 | U2 U3 | TPS54302 | 3.3 V 3 A buck (logic, sensors) | Texas Instruments | TPS54302DDCR | 296-47648-1-ND [verify] | SOT-23-6 | Top |  | 0.8 | 1.6
43 | 2 | U4 U5 | THVD1420 | RS-485 half duplex 12 Mbps, 3.3 V, +/-12 kV ESD, fail-safe receiver | Texas Instruments | THVD1420DR | 296-THVD1420DRCT-ND [verify] | SOIC-8_3.9x4.9mm_P1.27mm | Top |  | 1.6 | 3.2
44 | 1 | U6 | TPD4E05U06 | ESD 4-channel 0.5 pF, sensor I2C lines | Texas Instruments | TPD4E05U06DQAR | 296-30407-1-ND [verify] | USON-10_2.5x1.0mm_P0.5mm | Top |  | 0.5 | 0.5
45 | 1 | U7 | PC817 | Optocoupler: chiller alarm contact input (contact closes CHL_ALM to GND) | Sharp | PC817X2NSZ9F | PC817X2NSZ9F-ND [verify] | SMDIP-4_W9.53mm | Top |  | 0.3 | 0.3
46 | 1 | U8 | LM321 | Op-amp, set point amplifier x 3 (DAC 0-3.3 V -> 0-9.9 V) | Texas Instruments | LM321MF/NOPB | LM321MFNOPBCT-ND [verify] | SOT-23-5 | Top |  | 0.3 | 0.3
47 | 1 | U9 | 74AHCT1G125 | Buffer 3.3 V -> 5 V (TTL input), SK6812 data | Texas Instruments | SN74AHCT1G125DBVR | 296-4596-1-ND [verify] | SOT-23-5 | Top |  | 0.2 | 0.2
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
